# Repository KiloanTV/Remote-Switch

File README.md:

<div>
  <h1 align="center">Remote Switch</h1>

  <p align="center">
  <a href="https://blueprint.hackclub.com/">
    </img>
  </a>
  </p>
  <h1></h1>
  <p align="center">
    Turn on Devices without touching them. Simple but yet efficient!
  </p>
</div>

<sub align="center">This work is licensed under the
[MIT License](https://mit-license.org).
</sub>

## Table of Contents

- [About](#about)
- [Pictures](#pictures)
- [Bill of Materials](#bill-of-materials)

# About

I need a way to turn the PCs in my rack on and off, ideally centrally and via Wi-Fi. My idea is to use simple optocouplers to simulate the power button and control it with a microcontroller, just like the reset function. The positive LED output will then simply be connected to a GPIO pin of the MCU, allowing it to see whether the PC is on or off. Thats it!

# Pictures

# Bill of Materials

<details>
<summary><strong>Show Bill Of Materials(BOM) ----></strong></summary>

|Designator    |Footprint                                       |Quantity|Value                 |LCSC Part #|
|--------------|------------------------------------------------|--------|----------------------|-----------|
|J1            |PinHeader_2x03_P2.54mm_Horizontal               |1       |PC Header 1           |C41417351  |
|J2            |PinHeader_2x03_P2.54mm_Horizontal               |1       |PC Header 2           |C41417351  |
|J5            |Molex_Mini-Fit_Jr_5566-06A_2x03_P4.20mm_Vertical|1       |Power                 |C471417    |
|R1, R2, R3, R4|0805                                            |4       |R330                  |C17630     |
|U1            |WEMOS_C3_mini                                   |1       |WEMOS_C3_mini         |           |
|U2            |DIP-4_W7.62mm                                   |1       |EL817 - Power Switch 1|C5353      |
|U3            |DIP-4_W7.62mm                                   |1       |EL817 - Reset Switch 1|C5353      |
|U4            |DIP-4_W7.62mm                                   |1       |EL817 - Power Switch 2|C5353      |
|U5            |DIP-4_W7.62mm                                   |1       |EL817 - Reset Switch 2|C5353      |
|LCSC Quote: 14.32 Dollar      |                                                |        |                      |           |
|JLCPCB Quote: 6.54 Dollar     |                                                |        |                      |           |
|Aliexpress Quote: 5.69 Dollar |                                                |        |                      |           |
|All together: 26.55 Dollar    |                                                |        |                      |           |

</details>

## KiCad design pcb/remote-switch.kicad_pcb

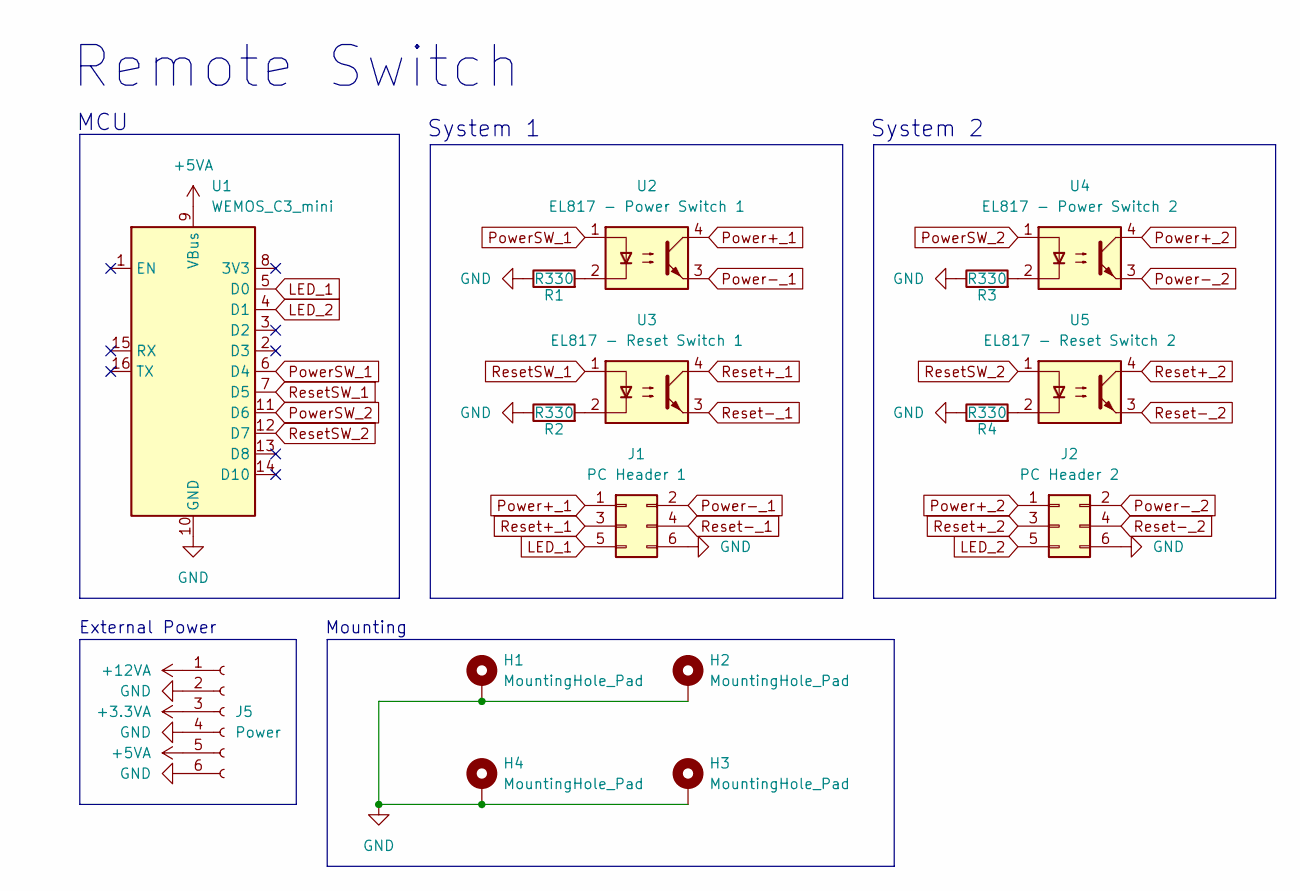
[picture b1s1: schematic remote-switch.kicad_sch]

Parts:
H1, H2, H3, H4: MountingHole_Pad; MountingHole_3.2mm_M3_Pad_Via
J1: PC Header 1; PinHeader_2x03_P2.54mm_Horizontal; LCSC C41417351
J2: PC Header 2; PinHeader_2x03_P2.54mm_Horizontal; LCSC C41417351
J5: Power; Molex_Mini-Fit_Jr_5566-06A_2x03_P4.20mm_Vertical; LCSC C471417
R1, R2, R3, R4: R330; R_0805_2012Metric_Pad1.20x1.40mm_HandSolder; LCSC C17630
U1: WEMOS_C3_mini
U2: EL817 - Power Switch 1; DIP-4_W7.62mm; LCSC C5353
U3: EL817 - Reset Switch 1; DIP-4_W7.62mm; LCSC C5353
U4: EL817 - Power Switch 2; DIP-4_W7.62mm; LCSC C5353
U5: EL817 - Reset Switch 2; DIP-4_W7.62mm; LCSC C5353

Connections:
+3.3VA: J5.3
+5VA: J5.5, U1.9 (VBus)
+12VA: J5.1
GND: H1.1, H2.1, H3.1, H4.1, J1.6, J2.6, J5.2, J5.4, J5.6, R1.1, R2.1, R3.1, R4.1, U1.10 (GND)
LED_1: J1.5, U1.5 (D0)
LED_2: J2.5, U1.4 (D1)
unnamed: R1.2, U2.2
unnamed: R2.2, U3.2
unnamed: R3.2, U4.2
unnamed: R4.2, U5.2
Power+_1: J1.1, U2.4
Power+_2: J2.1, U4.4
Power-_1: J1.2, U2.3
Power-_2: J2.2, U4.3
PowerSW_1: U1.6 (D4), U2.1
PowerSW_2: U1.11 (D6), U4.1
Reset+_1: J1.3, U3.4
Reset+_2: J2.3, U5.4
Reset-_1: J1.4, U3.3
Reset-_2: J2.4, U5.3
ResetSW_1: U1.7 (D5), U3.1
ResetSW_2: U1.12 (D7), U5.1

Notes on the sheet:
System 2
System 1
MCU
Mounting
External Power
Remote Switch

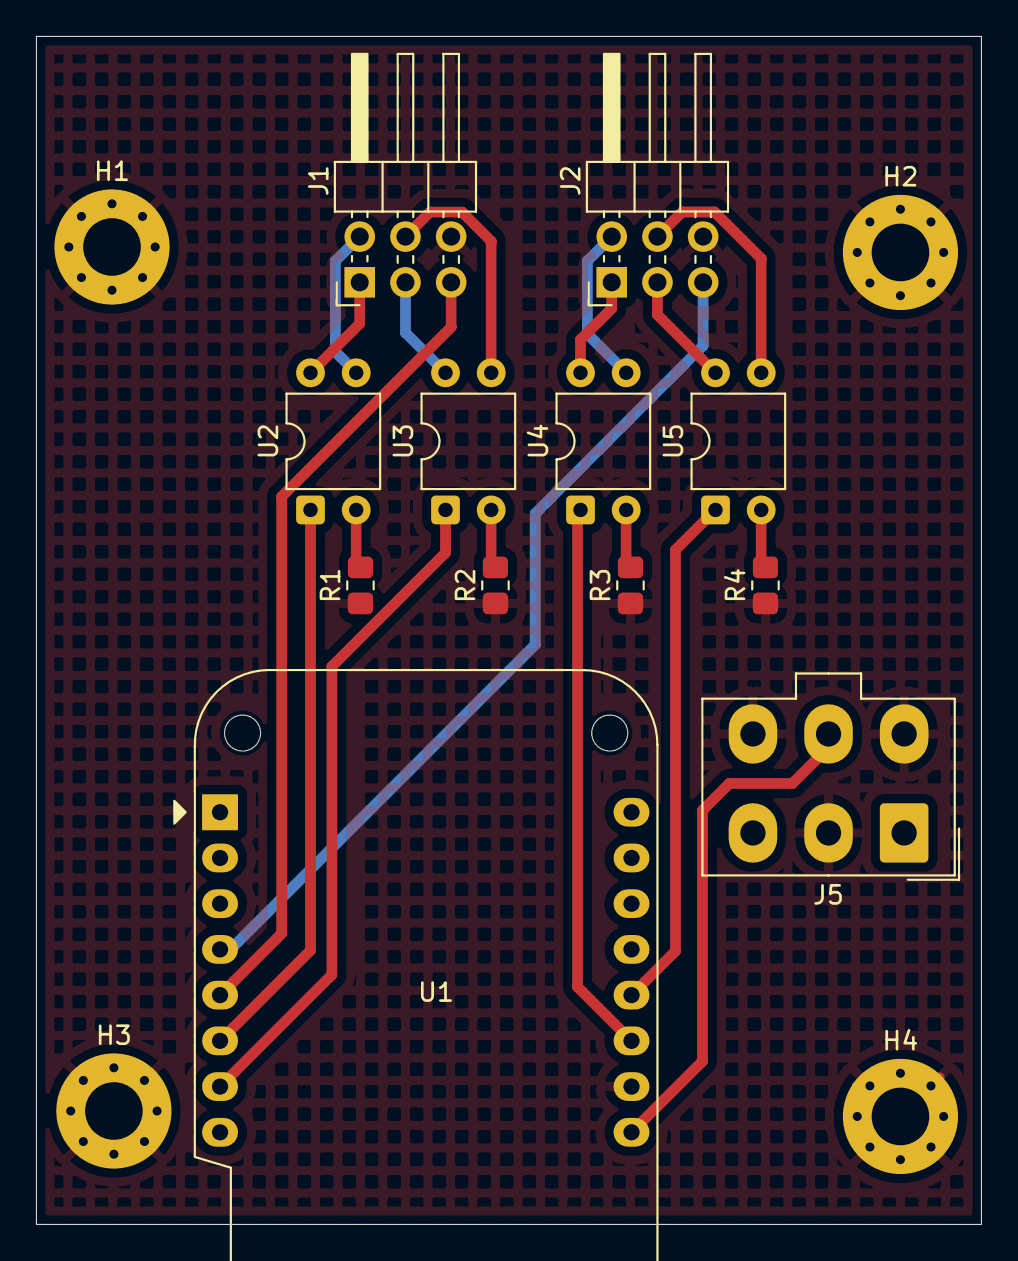
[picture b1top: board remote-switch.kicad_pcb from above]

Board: 2 copper layers, 52.5 x 66.0 mm, 16 parts (0 on the bottom side), 20 nets.

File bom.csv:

Designator,Footprint,Quantity,Value,LCSC Part #,AliExpress Link
J1,PinHeader_2x03_P2.54mm_Horizontal,1,PC Header 1,C41417351,
J2,PinHeader_2x03_P2.54mm_Horizontal,1,PC Header 2,C41417351,
J5,Molex_Mini-Fit_Jr_5566-06A_2x03_P4.20mm_Vertical,1,Power,C471417,
"R1, R2, R3, R4",0805,4,R330,C17630,
U1,WEMOS_C3_mini,1,WEMOS_C3_mini,,https://de.aliexpress.com/item/1005004740051202.html
U2,DIP-4_W7.62mm,1,EL817 - Power Switch 1,C5353,
U3,DIP-4_W7.62mm,1,EL817 - Reset Switch 1,C5353,
U4,DIP-4_W7.62mm,1,EL817 - Power Switch 2,C5353,
U5,DIP-4_W7.62mm,1,EL817 - Reset Switch 2,C5353,
LCSC Quote: 14.32 Dollar,,,,,
JLCPCB Quote: 6.54 Dollar,,,,,
Aliexpress Quote: 5.69 Dollar,,,,,
All together: 26.55 Dollar,,,,,

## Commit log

2025-12-07 add files
    _ Kian
2025-12-07 revision
    _ Kian
2025-12-07 add .csv files
    _ Kian
2025-12-25 add simple firmware
    _ Kian
